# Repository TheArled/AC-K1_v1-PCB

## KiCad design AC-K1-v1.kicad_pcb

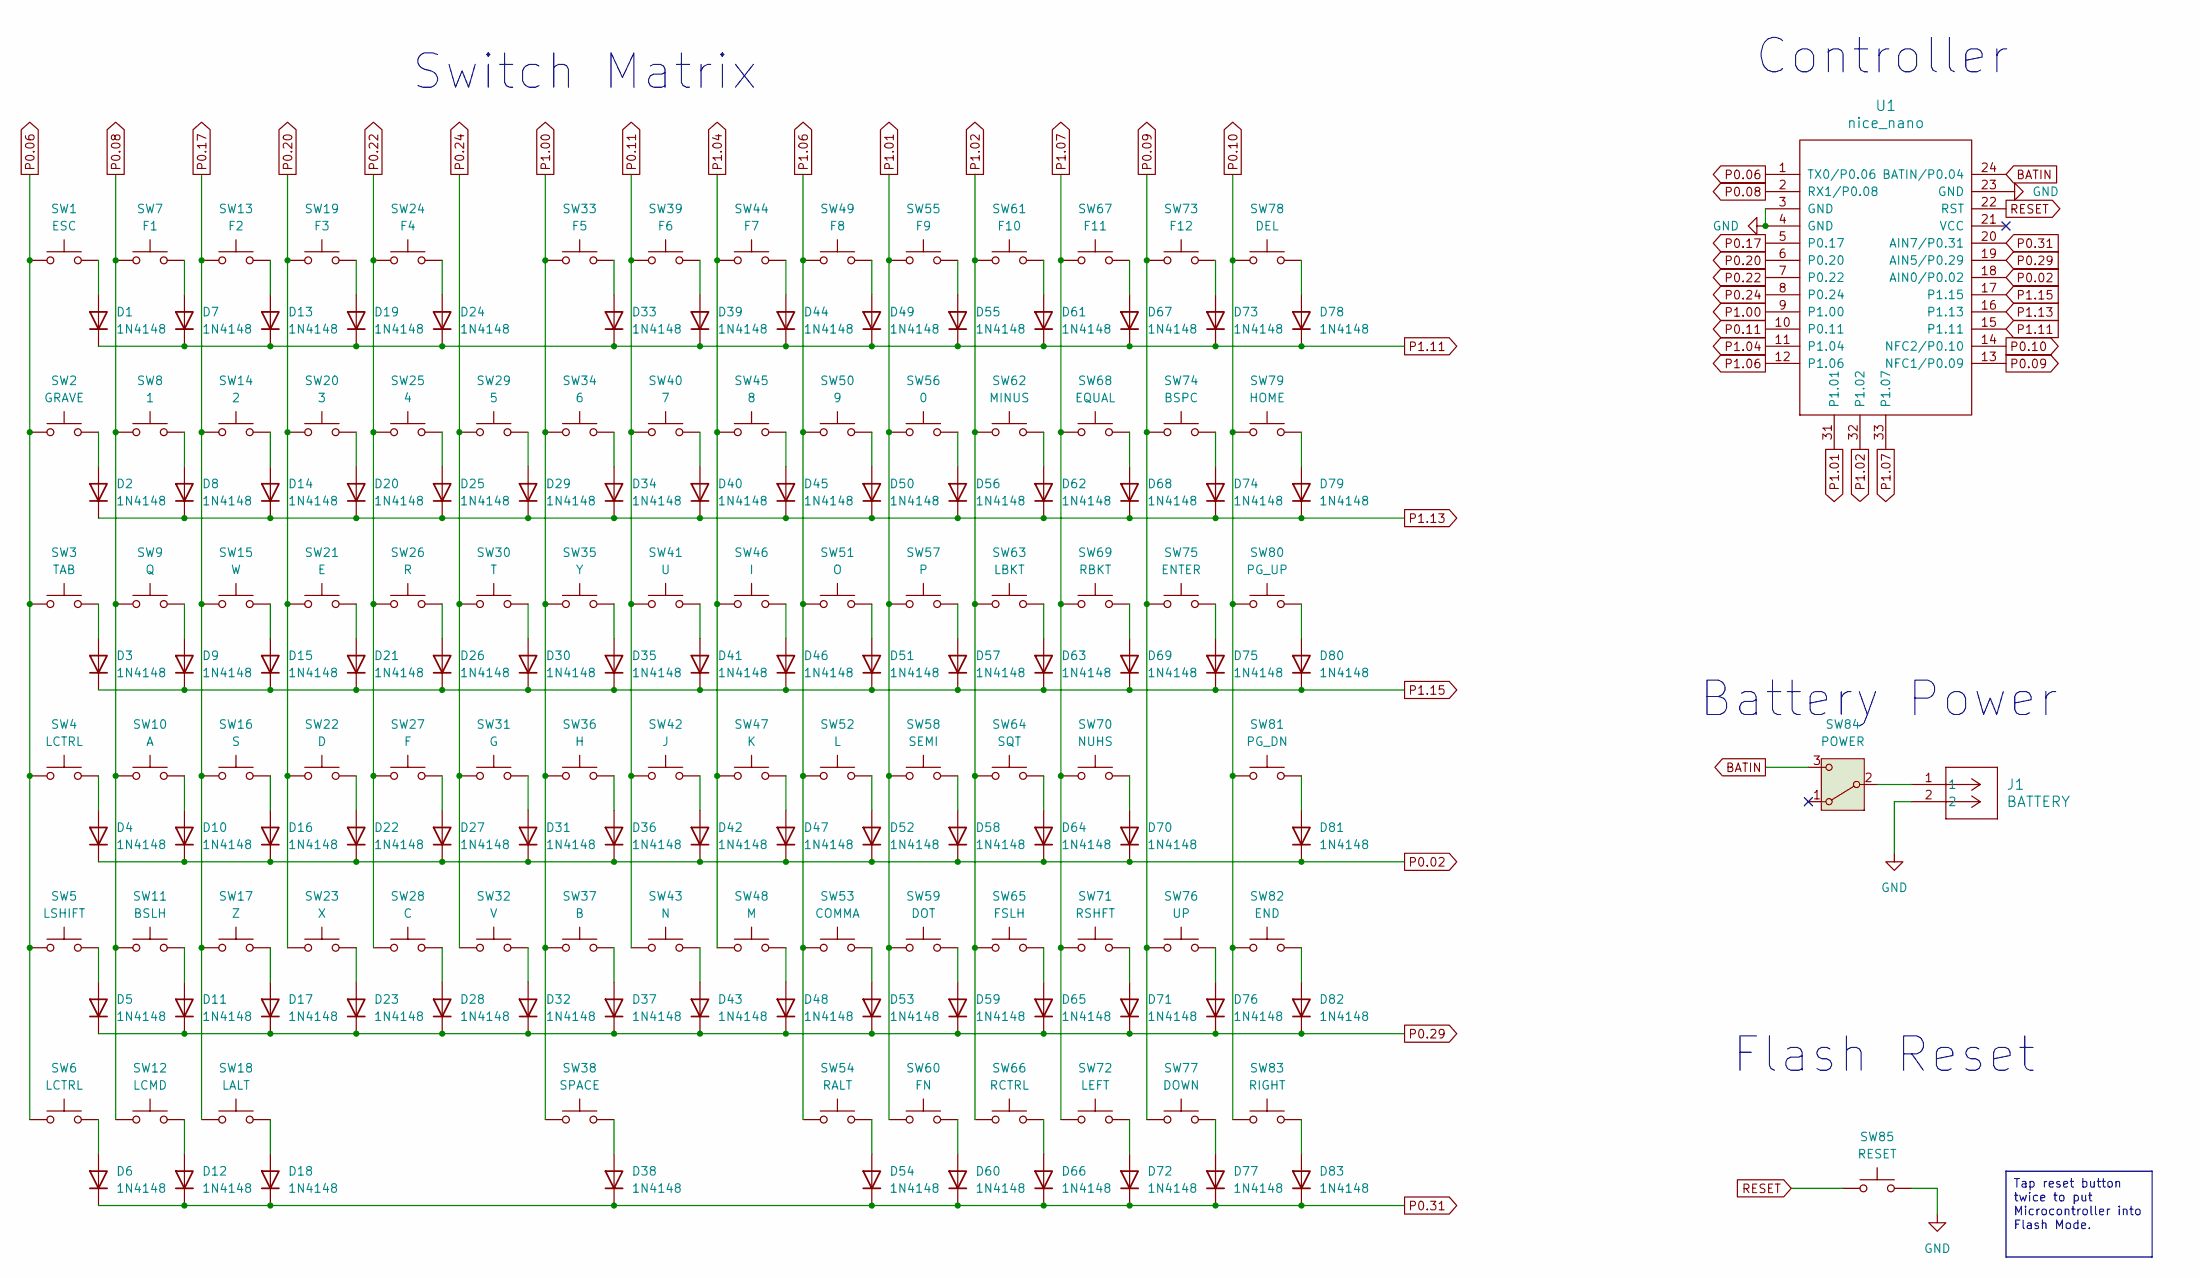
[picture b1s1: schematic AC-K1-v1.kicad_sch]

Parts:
D1, D2, D3, D4, D5, D6, D7, D8, D9, D10, D11, D12, D13, D14, D15, D16, D17, D18, D19, D20, D21, D22, D23, D24, D25, D26, D27, D28, D29, D30, D31, D32, D33, D34, D35, D36, D37, D38, D39, D40, D41, D42, D43, D44, D45, D46, D47, D48, D49, D50, D51, D52, D53, D54, D55, D56, D57, D58, D59, D60, D61, D62, D63, D64, D65, D66, D67, D68, D69, D70, D71, D72, D73, D74, D75, D76, D77, D78, D79, D80, D81, D82, D83: 1N4148; D_DO-35_SOD27_P7.62mm_Horizontal
J1: BATTERY; JST_PH_S2B-PH-K_1x02_P2.00mm_Horizontal
SW1: ESC; SW_Kailh_Choc_V1_1.00u_Spacing
SW2: GRAVE; SW_Kailh_Choc_V1_1.00u_Spacing
SW3: TAB; SW_Kailh_Choc_V1_1.50u_Spacing
SW4: LCTRL; SW_Kailh_Choc_V1_1.75u_Spacing
SW5: LSHIFT; SW_Kailh_Choc_V1_1.50u_Spacing
SW6: LCTRL; SW_Kailh_Choc_V1_1.50u_Spacing
SW7: F1; SW_Kailh_Choc_V1_1.00u_Spacing
SW8: 1; SW_Kailh_Choc_V1_1.00u_Spacing
SW9: Q; SW_Kailh_Choc_V1_1.00u_Spacing
SW10: A; SW_Kailh_Choc_V1_1.00u_Spacing
SW11: BSLH; SW_Kailh_Choc_V1_1.00u_Spacing
SW12: LCMD; SW_Kailh_Choc_V1_1.25u_Spacing
SW13: F2; SW_Kailh_Choc_V1_1.00u_Spacing
SW14: 2; SW_Kailh_Choc_V1_1.00u_Spacing
SW15: W; SW_Kailh_Choc_V1_1.00u_Spacing
SW16: S; SW_Kailh_Choc_V1_1.00u_Spacing
SW17: Z; SW_Kailh_Choc_V1_1.00u_Spacing
SW18: LALT; SW_Kailh_Choc_V1_1.25u_Spacing
SW19: F3; SW_Kailh_Choc_V1_1.00u_Spacing
SW20: 3; SW_Kailh_Choc_V1_1.00u_Spacing
SW21: E; SW_Kailh_Choc_V1_1.00u_Spacing
SW22: D; SW_Kailh_Choc_V1_1.00u_Spacing
SW23: X; SW_Kailh_Choc_V1_1.00u_Spacing
SW24: F4; SW_Kailh_Choc_V1_1.00u_Spacing
SW25: 4; SW_Kailh_Choc_V1_1.00u_Spacing
SW26: R; SW_Kailh_Choc_V1_1.00u_Spacing
SW27: F; SW_Kailh_Choc_V1_1.00u_Spacing
SW28: C; SW_Kailh_Choc_V1_1.00u_Spacing
SW29: 5; SW_Kailh_Choc_V1_1.00u_Spacing
SW30: T; SW_Kailh_Choc_V1_1.00u_Spacing
SW31: G; SW_Kailh_Choc_V1_1.00u_Spacing
SW32: V; SW_Kailh_Choc_V1_1.00u_Spacing
SW33: F5; SW_Kailh_Choc_V1_1.00u_Spacing
SW34: 6; SW_Kailh_Choc_V1_1.00u_Spacing
SW35: Y; SW_Kailh_Choc_V1_1.00u_Spacing
SW36: H; SW_Kailh_Choc_V1_1.00u_Spacing
SW37: B; SW_Kailh_Choc_V1_1.00u_Spacing
SW38: SPACE; SW_Kailh_Choc_V1_5.50u_Spacing
SW39: F6; SW_Kailh_Choc_V1_1.00u_Spacing
SW40: 7; SW_Kailh_Choc_V1_1.00u_Spacing
SW41: U; SW_Kailh_Choc_V1_1.00u_Spacing
SW42: J; SW_Kailh_Choc_V1_1.00u_Spacing
SW43: N; SW_Kailh_Choc_V1_1.00u_Spacing
SW44: F7; SW_Kailh_Choc_V1_1.00u_Spacing
SW45: 8; SW_Kailh_Choc_V1_1.00u_Spacing
SW46: I; SW_Kailh_Choc_V1_1.00u_Spacing
SW47: K; SW_Kailh_Choc_V1_1.00u_Spacing
SW48: M; SW_Kailh_Choc_V1_1.00u_Spacing
SW49: F8; SW_Kailh_Choc_V1_1.00u_Spacing
SW50: 9; SW_Kailh_Choc_V1_1.00u_Spacing
SW51: O; SW_Kailh_Choc_V1_1.00u_Spacing
SW52: L; SW_Kailh_Choc_V1_1.00u_Spacing
SW53: COMMA; SW_Kailh_Choc_V1_1.00u_Spacing
SW54: RALT; SW_Kailh_Choc_V1_1.25u_Spacing
SW55: F9; SW_Kailh_Choc_V1_1.00u_Spacing
SW56: 0; SW_Kailh_Choc_V1_1.00u_Spacing
SW57: P; SW_Kailh_Choc_V1_1.00u_Spacing
SW58: SEMI; SW_Kailh_Choc_V1_1.00u_Spacing
SW59: DOT; SW_Kailh_Choc_V1_1.00u_Spacing
SW60: FN; SW_Kailh_Choc_V1_1.25u_Spacing
SW61: F10; SW_Kailh_Choc_V1_1.00u_Spacing
SW62: MINUS; SW_Kailh_Choc_V1_1.00u_Spacing
SW63: LBKT; SW_Kailh_Choc_V1_1.00u_Spacing
SW64: SQT; SW_Kailh_Choc_V1_1.00u_Spacing
SW65: FSLH; SW_Kailh_Choc_V1_1.00u_Spacing
SW66: RCTRL; SW_Kailh_Choc_V1_1.25u_Spacing
SW67: F11; SW_Kailh_Choc_V1_1.00u_Spacing
SW68: EQUAL; SW_Kailh_Choc_V1_1.00u_Spacing
SW69: RBKT; SW_Kailh_Choc_V1_1.00u_Spacing
SW70: NUHS; SW_Kailh_Choc_V1_1.00u_Spacing
SW71: RSHFT; SW_Kailh_Choc_V1_1.50u_Spacing
SW72: LEFT; SW_Kailh_Choc_V1_1.00u_Spacing
SW73: F12; SW_Kailh_Choc_V1_1.00u_Spacing
SW74: BSPC; SW_Kailh_Choc_V1_1.00u_Spacing
SW75: ENTER; SW_Kailh_Choc_V1_ISOEnter_Spacing
SW76: UP; SW_Kailh_Choc_V1_1.00u_Spacing
SW77: DOWN; SW_Kailh_Choc_V1_1.00u_Spacing
SW78: DEL; SW_Kailh_Choc_V1_1.00u_Spacing
SW79: HOME; SW_Kailh_Choc_V1_1.00u_Spacing
SW80: PG_UP; SW_Kailh_Choc_V1_1.00u_Spacing
SW81: PG_DN; SW_Kailh_Choc_V1_1.00u_Spacing
SW82: END; SW_Kailh_Choc_V1_1.00u_Spacing
SW83: RIGHT; SW_Kailh_Choc_V1_1.00u_Spacing
SW84: POWER; SW_Slide_SPDT_Angled_CK_OS102011MA1Q
SW85: RESET; SW_PUSH_1P1T_6x3.5mm_H4.3_APEM_MJTP1243
U1: nice_nano

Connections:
BATIN: SW84.3 (C), U1.24 (BATIN/P0.04)
GND: J1.2, SW85.2, U1.3 (GND), U1.4 (GND), U1.23 (GND)
unnamed: D1.2 (A), SW1.2
unnamed: D2.2 (A), SW2.2
unnamed: D3.2 (A), SW3.2
unnamed: D4.2 (A), SW4.2
unnamed: D5.2 (A), SW5.2
unnamed: D6.2 (A), SW6.2
unnamed: D7.2 (A), SW7.2
unnamed: D8.2 (A), SW8.2
unnamed: D9.2 (A), SW9.2
unnamed: D10.2 (A), SW10.2
unnamed: D11.2 (A), SW11.2
unnamed: D12.2 (A), SW12.2
unnamed: D13.2 (A), SW13.2
unnamed: D14.2 (A), SW14.2
unnamed: D15.2 (A), SW15.2
unnamed: D16.2 (A), SW16.2
unnamed: D17.2 (A), SW17.2
unnamed: D18.2 (A), SW18.2
unnamed: D19.2 (A), SW19.2
unnamed: D20.2 (A), SW20.2
unnamed: D21.2 (A), SW21.2
unnamed: D22.2 (A), SW22.2
unnamed: D23.2 (A), SW23.2
unnamed: D24.2 (A), SW24.2
unnamed: D25.2 (A), SW25.2
unnamed: D26.2 (A), SW26.2
unnamed: D27.2 (A), SW27.2
unnamed: D28.2 (A), SW28.2
unnamed: D29.2 (A), SW29.2
unnamed: D30.2 (A), SW30.2
unnamed: D31.2 (A), SW31.2
unnamed: D32.2 (A), SW32.2
unnamed: D33.2 (A), SW33.2
unnamed: D34.2 (A), SW34.2
unnamed: D35.2 (A), SW35.2
unnamed: D36.2 (A), SW36.2
unnamed: D37.2 (A), SW37.2
unnamed: D38.2 (A), SW38.2
unnamed: D39.2 (A), SW39.2
unnamed: D40.2 (A), SW40.2
unnamed: D41.2 (A), SW41.2
unnamed: D42.2 (A), SW42.2
unnamed: D43.2 (A), SW43.2
unnamed: D44.2 (A), SW44.2
unnamed: D45.2 (A), SW45.2
unnamed: D46.2 (A), SW46.2
unnamed: D47.2 (A), SW47.2
unnamed: D48.2 (A), SW48.2
unnamed: D49.2 (A), SW49.2
unnamed: D50.2 (A), SW50.2
unnamed: D51.2 (A), SW51.2
unnamed: D52.2 (A), SW52.2
unnamed: D53.2 (A), SW53.2
unnamed: D54.2 (A), SW54.2
unnamed: D55.2 (A), SW55.2
unnamed: D56.2 (A), SW56.2
unnamed: D57.2 (A), SW57.2
unnamed: D58.2 (A), SW58.2
unnamed: D59.2 (A), SW59.2
unnamed: D60.2 (A), SW60.2
unnamed: D61.2 (A), SW61.2
unnamed: D62.2 (A), SW62.2
unnamed: D63.2 (A), SW63.2
unnamed: D64.2 (A), SW64.2
unnamed: D65.2 (A), SW65.2
unnamed: D66.2 (A), SW66.2
unnamed: D67.2 (A), SW67.2
unnamed: D68.2 (A), SW68.2
unnamed: D69.2 (A), SW69.2
unnamed: D70.2 (A), SW70.2
unnamed: D71.2 (A), SW71.2
unnamed: D72.2 (A), SW72.2
unnamed: D73.2 (A), SW73.2
unnamed: D74.2 (A), SW74.2
unnamed: D75.2 (A), SW75.2
unnamed: D76.2 (A), SW76.2
unnamed: D77.2 (A), SW77.2
unnamed: D78.2 (A), SW78.2
unnamed: D79.2 (A), SW79.2
unnamed: D80.2 (A), SW80.2
unnamed: D81.2 (A), SW81.2
unnamed: D82.2 (A), SW82.2
unnamed: D83.2 (A), SW83.2
unnamed: J1.1, SW84.2 (B)
P0.02: D4.1 (K), D10.1 (K), D16.1 (K), D22.1 (K), D27.1 (K), D31.1 (K), D36.1 (K), D42.1 (K), D47.1 (K), D52.1 (K), D58.1 (K), D64.1 (K), D70.1 (K), D81.1 (K), U1.18 (AIN0/P0.02)
P0.06: SW1.1, SW2.1, SW3.1, SW4.1, SW5.1, SW6.1, U1.1 (TX0/P0.06)
P0.08: SW7.1, SW8.1, SW9.1, SW10.1, SW11.1, SW12.1, U1.2 (RX1/P0.08)
P0.09: SW73.1, SW74.1, SW75.1, SW76.1, SW77.1, U1.13 (NFC1/P0.09)
P0.10: SW78.1, SW79.1, SW80.1, SW81.1, SW82.1, SW83.1, U1.14 (NFC2/P0.10)
P0.11: SW39.1, SW40.1, SW41.1, SW42.1, SW43.1, U1.10 (P0.11)
P0.17: SW13.1, SW14.1, SW15.1, SW16.1, SW17.1, SW18.1, U1.5 (P0.17)
P0.20: SW19.1, SW20.1, SW21.1, SW22.1, SW23.1, U1.6 (P0.20)
P0.22: SW24.1, SW25.1, SW26.1, SW27.1, SW28.1, U1.7 (P0.22)
P0.24: SW29.1, SW30.1, SW31.1, SW32.1, U1.8 (P0.24)
P0.29: D5.1 (K), D11.1 (K), D17.1 (K), D23.1 (K), D28.1 (K), D32.1 (K), D37.1 (K), D43.1 (K), D48.1 (K), D53.1 (K), D59.1 (K), D65.1 (K), D71.1 (K), D76.1 (K), D82.1 (K), U1.19 (AIN5/P0.29)
P0.31: D6.1 (K), D12.1 (K), D18.1 (K), D38.1 (K), D54.1 (K), D60.1 (K), D66.1 (K), D72.1 (K), D77.1 (K), D83.1 (K), U1.20 (AIN7/P0.31)
P1.00: SW33.1, SW34.1, SW35.1, SW36.1, SW37.1, SW38.1, U1.9 (P1.00)
P1.01: SW55.1, SW56.1, SW57.1, SW58.1, SW59.1, SW60.1, U1.31 (P1.01)
P1.02: SW61.1, SW62.1, SW63.1, SW64.1, SW65.1, SW66.1, U1.32 (P1.02)
P1.04: SW44.1, SW45.1, SW46.1, SW47.1, SW48.1, U1.11 (P1.04)
P1.06: SW49.1, SW50.1, SW51.1, SW52.1, SW53.1, SW54.1, U1.12 (P1.06)
P1.07: SW67.1, SW68.1, SW69.1, SW70.1, SW71.1, SW72.1, U1.33 (P1.07)
P1.11: D1.1 (K), D7.1 (K), D13.1 (K), D19.1 (K), D24.1 (K), D33.1 (K), D39.1 (K), D44.1 (K), D49.1 (K), D55.1 (K), D61.1 (K), D67.1 (K), D73.1 (K), D78.1 (K), U1.15 (P1.11)
P1.13: D2.1 (K), D8.1 (K), D14.1 (K), D20.1 (K), D25.1 (K), D29.1 (K), D34.1 (K), D40.1 (K), D45.1 (K), D50.1 (K), D56.1 (K), D62.1 (K), D68.1 (K), D74.1 (K), D79.1 (K), U1.16 (P1.13)
P1.15: D3.1 (K), D9.1 (K), D15.1 (K), D21.1 (K), D26.1 (K), D30.1 (K), D35.1 (K), D41.1 (K), D46.1 (K), D51.1 (K), D57.1 (K), D63.1 (K), D69.1 (K), D75.1 (K), D80.1 (K), U1.17 (P1.15)
RESET: SW85.1, U1.22 (RST)

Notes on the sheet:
Tap reset button twice to put Microcontroller into Flash Mode.
Battery Power
Switch Matrix
Controller
Flash Reset

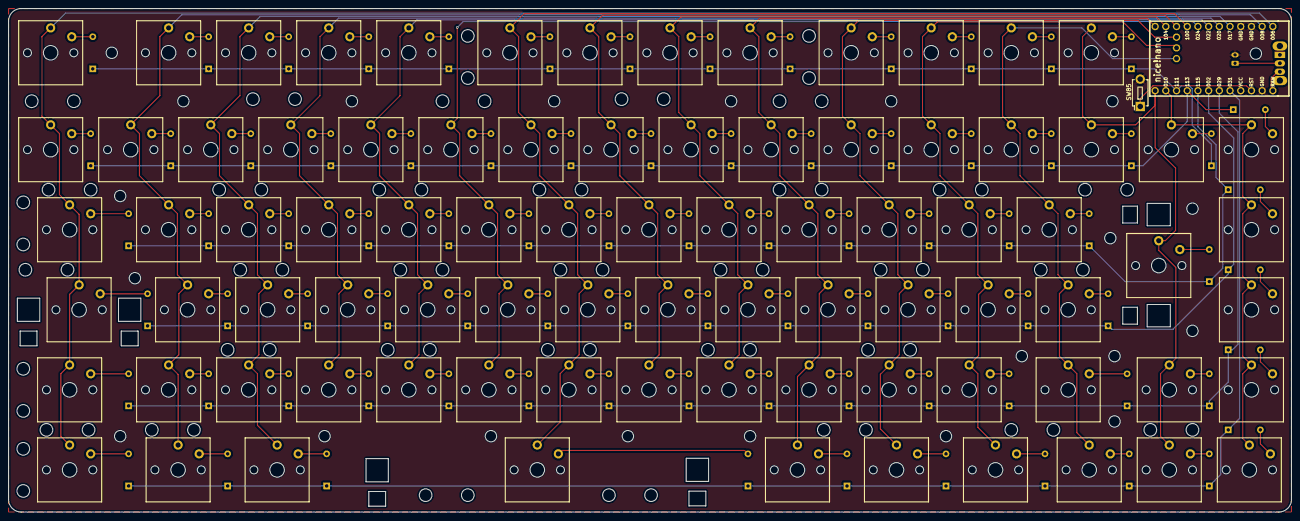
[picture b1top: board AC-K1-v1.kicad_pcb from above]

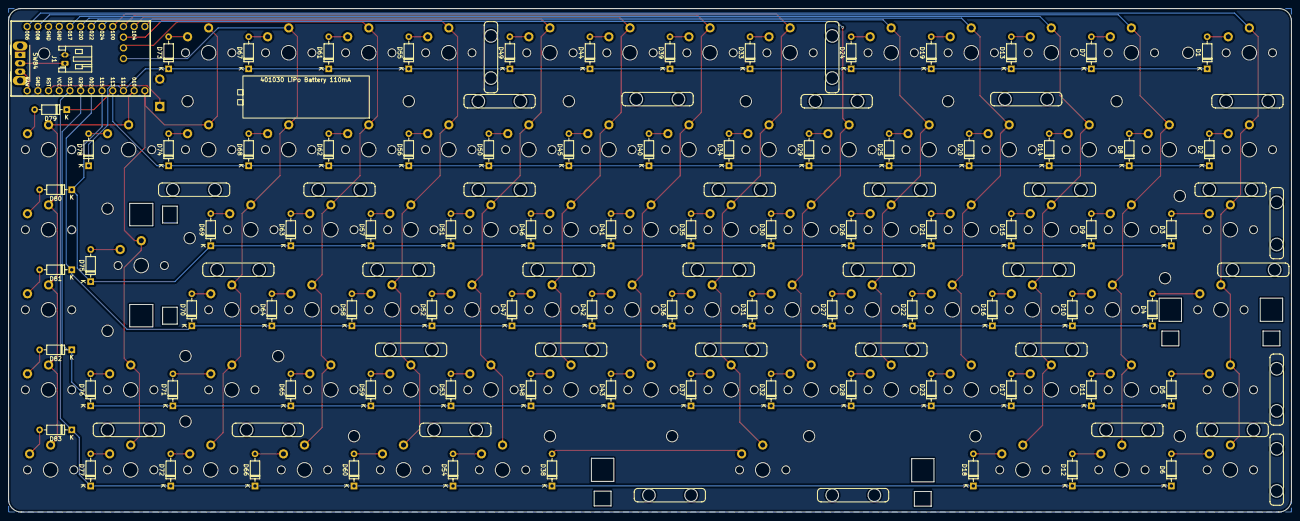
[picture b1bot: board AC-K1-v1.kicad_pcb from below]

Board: 2 copper layers, 304.4 x 119.4 mm, 193 parts (86 on the bottom side), 108 nets.

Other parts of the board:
1, 2, 4, 5, 6, 7, 8, 9, 10, 11, 13, 14, 15, 16, 18, 19, 20, 21, 22, 23, 27, 50: MountingHole_2.7mm_M2.5_with_spacer
Battery1: 401030 Lipo Battery Size

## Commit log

2024-06-16 Added New KiCad Project
2024-06-16 Added Module Libraries
2024-06-16 Added new Library
2024-07-06 Worked on spreadsheet
2024-07-09 Made big part of PCB
2024-07-09 Fixed wire missing
2024-07-09 Fixed nice nano labels positions
2024-07-09 Added screw holes and improved lanes a little
2024-07-11 Redoing everything
2024-07-11 Added spacings to keycaps for easier alignment
2024-07-11 Made some changes
2024-07-11 Used fork to have spaced switches
2024-07-11 Started positioning switches
2024-07-12 Added new library with stabilizers
2024-07-12 Finished positioning switches
2024-07-12 Started pulling lanes
2024-07-13 Made Column traces
2024-07-13 Thinking about moving battery and connector below spacebar
2024-07-13 Finished most work, now screwsholes are missing
2024-07-13 Some switches got stabilizers now
2024-07-16 Reactivated layers
2024-07-16 Made small changes in routing.
2024-07-24 PCB Almost finished
2024-07-27 latest changes
2024-07-31 Adjusted screws
2024-07-31 Added top ground zone and changed screw positions
2024-08-10 Added graphics to pcb
2024-08-10 Added serial number label
2024-08-12 Unhidden Supports
